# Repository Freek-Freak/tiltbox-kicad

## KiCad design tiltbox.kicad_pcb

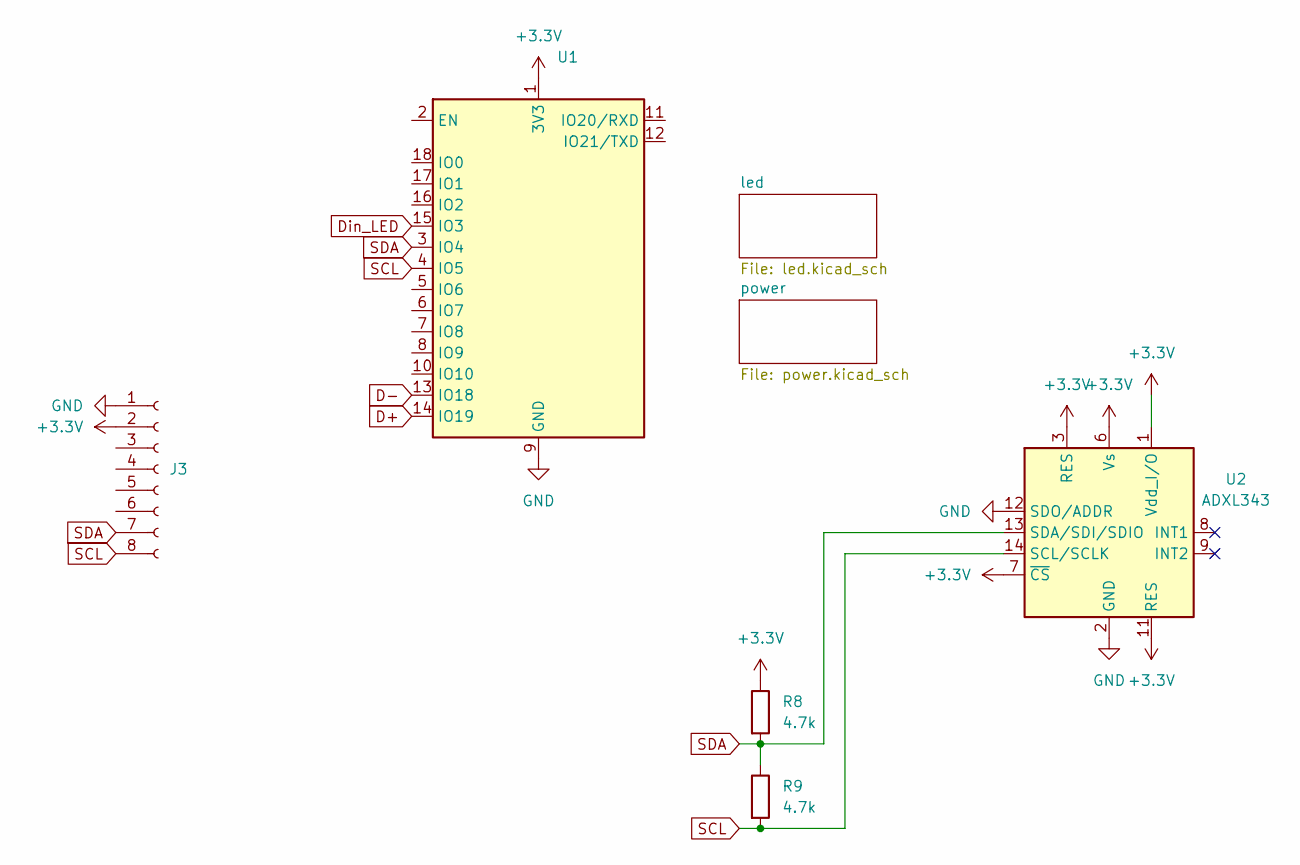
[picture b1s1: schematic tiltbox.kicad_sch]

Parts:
J3: Conn_01x08_Socket; PinHeader_1x08_P2.54mm_Vertical
R8, R9: 4.7k
U1: ESP32-C3-WROOM-02
U2: ADXL343; LGA-14_3x5mm_P0.8mm_LayoutBorder1x6y

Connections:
+3.3V: J3.2, R8.1, U1.1 (3V3), U2.1 (Vdd_I/O), U2.3 (RES), U2.6 (Vs), U2.7 (~CS), U2.11 (RES); also elsewhere on the board
D+: U1.14 (IO19); also elsewhere on the board
D-: U1.13 (IO18); also elsewhere on the board
Din_LED: U1.15 (IO3); also elsewhere on the board
GND: J3.1, U1.9 (GND), U1.19 (GND), U2.2 (GND), U2.4 (GND), U2.5 (GND), U2.12 (SDO/ADDR); also elsewhere on the board
SCL: J3.8, R9.2, U1.4 (IO5), U2.14 (SCL/SCLK)
SDA: J3.7, R8.2, R9.1, U1.3 (IO4), U2.13 (SDA/SDI/SDIO)

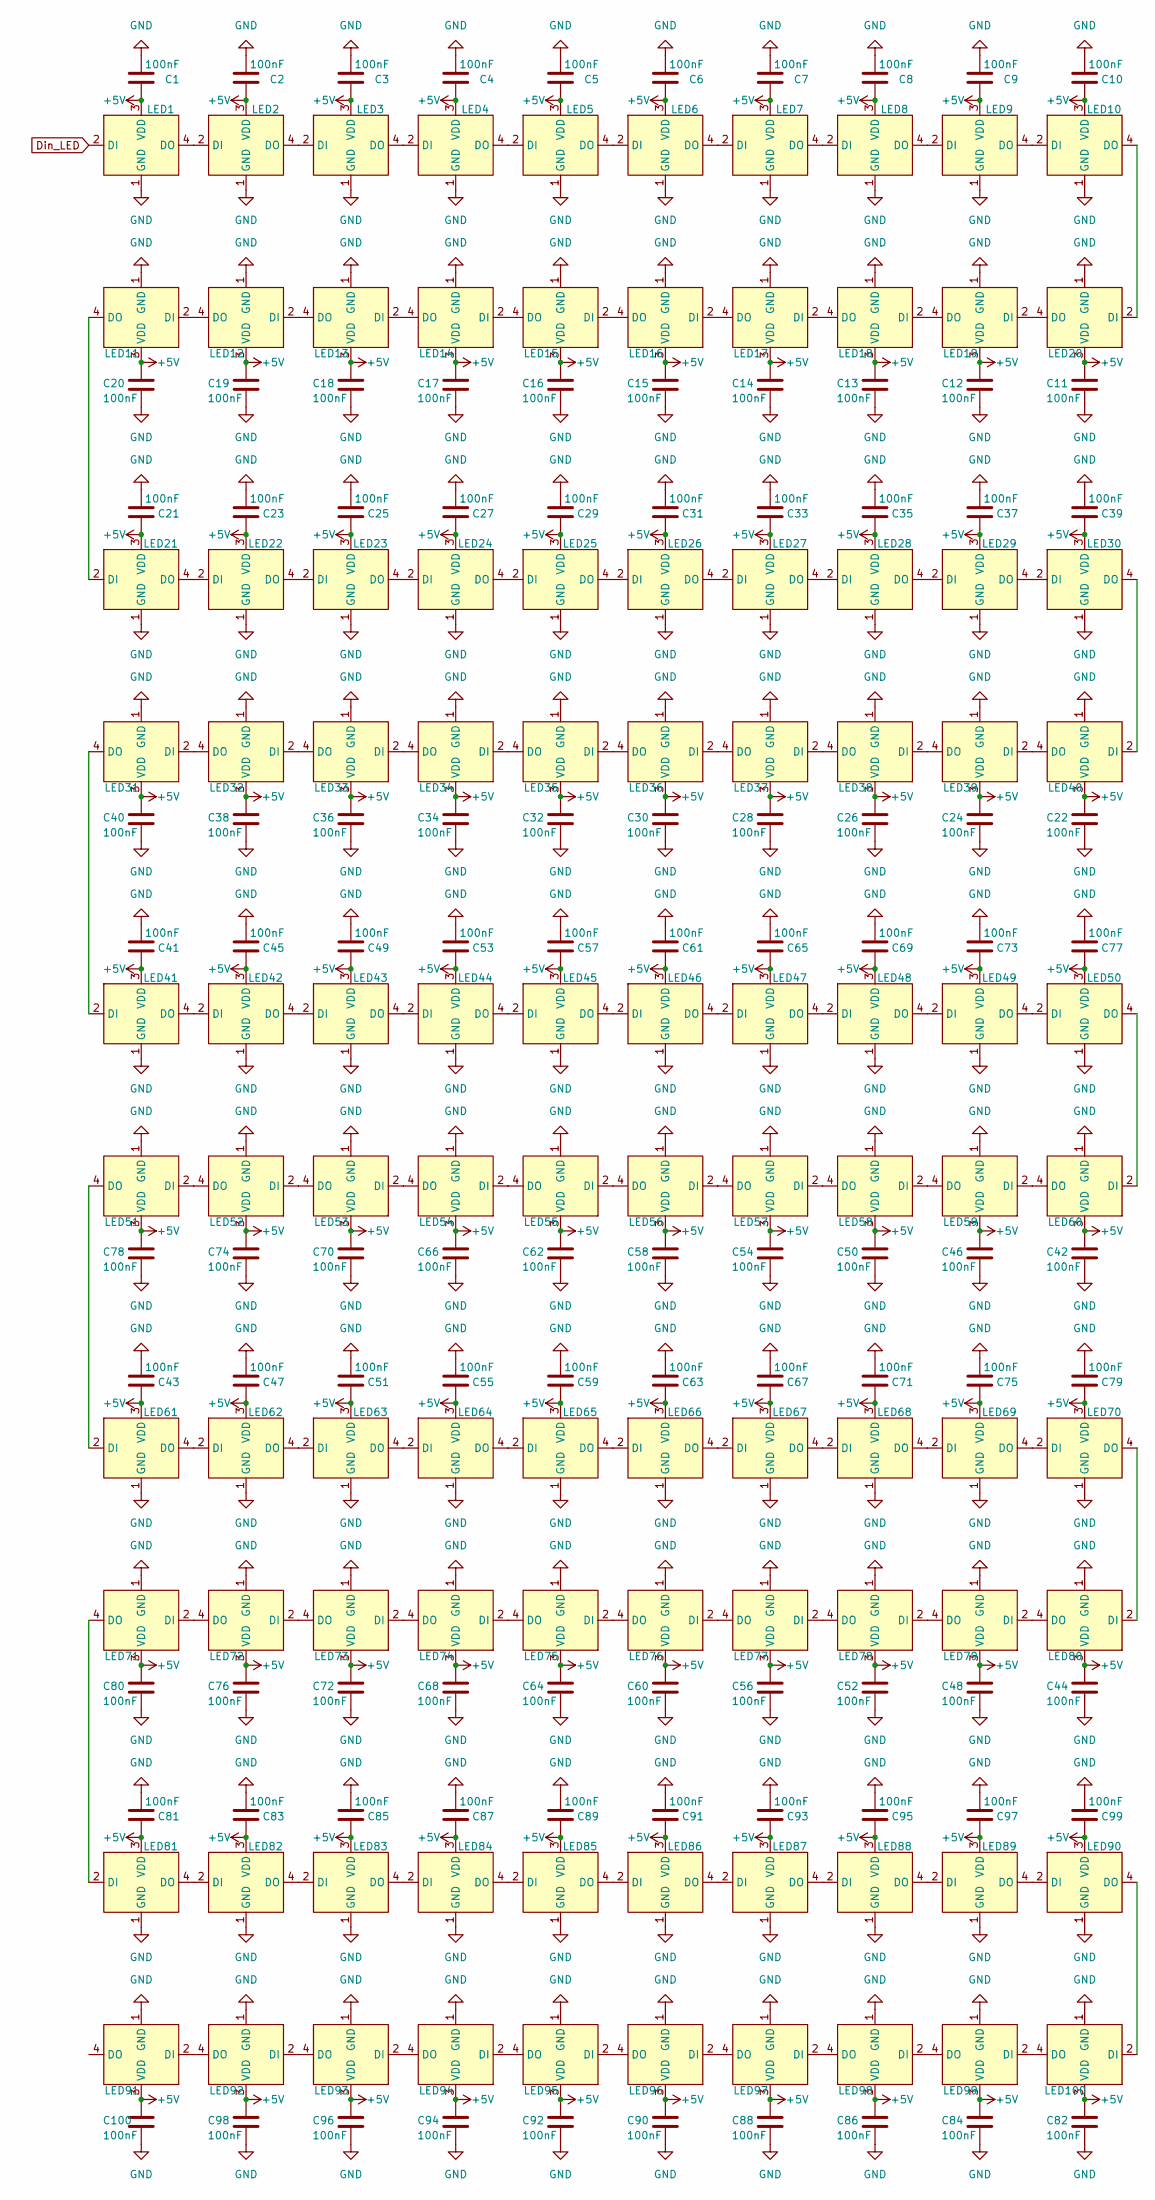
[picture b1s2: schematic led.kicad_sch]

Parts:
C1, C2, C3, C4, C5, C6, C7, C8, C9, C10, C11, C12, C13, C14, C15, C16, C17, C18, C19, C20, C21, C22, C23, C24, C25, C26, C27, C28, C29, C30, C31, C32, C33, C34, C35, C36, C37, C38, C39, C40, C41, C42, C43, C44, C45, C46, C47, C48, C49, C50, C51, C52, C53, C54, C55, C56, C57, C58, C59, C60, C61, C62, C63, C64, C65, C66, C67, C68, C69, C70, C71, C72, C73, C74, C75, C76, C77, C78, C79, C80, C81, C82, C83, C84, C85, C86, C87, C88, C89, C90, C91, C92, C93, C94, C95, C96, C97, C98, C99, C100: 100nF; C_0603_1608Metric; LCSC C14663
LED1, LED2, LED3, LED4, LED5, LED6, LED7, LED8, LED9, LED10, LED11, LED12, LED13, LED14, LED15, LED16, LED17, LED18, LED19, LED20, LED21, LED22, LED23, LED24, LED25, LED26, LED27, LED28, LED29, LED30, LED31, LED32, LED33, LED34, LED35, LED36, LED37, LED38, LED39, LED40, LED41, LED42, LED43, LED44, LED45, LED46, LED47, LED48, LED49, LED50, LED51, LED52, LED53, LED54, LED55, LED56, LED57, LED58, LED59, LED60, LED61, LED62, LED63, LED64, LED65, LED66, LED67, LED68, LED69, LED70, LED71, LED72, LED73, LED74, LED75, LED76, LED77, LED78, LED79, LED80, LED81, LED82, LED83, LED84, LED85, LED86, LED87, LED88, LED89, LED90, LED91, LED92, LED93, LED94, LED95, LED96, LED97, LED98, LED99, LED100: XL-3528RGBW-WS2812B; LED_WS2812B-Mini_PLCC4_3.5x3.5mm; LCSC C2890364

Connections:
+5V: C1.2, C2.2, C3.2, C4.2, C5.2, C6.2, C7.2, C8.2, C9.2, C10.2, C11.2, C12.2, C13.2, C14.2, C15.2, C16.2, C17.2, C18.2, C19.2, C20.2, C21.2, C22.2, C23.2, C24.2, C25.2, C26.2, C27.2, C28.2, C29.2, C30.2, C31.2, C32.2, C33.2, C34.2, C35.2, C36.2, C37.2, C38.2, C39.2, C40.2, C41.2, C42.2, C43.2, C44.2, C45.2, C46.2, C47.2, C48.2, C49.2, C50.2, C51.2, C52.2, C53.2, C54.2, C55.2, C56.2, C57.2, C58.2, C59.2, C60.2, C61.2, C62.2, C63.2, C64.2, C65.2, C66.2, C67.2, C68.2, C69.2, C70.2, C71.2, C72.2, C73.2, C74.2, C75.2, C76.2, C77.2, C78.2, C79.2, C80.2, C81.2, C82.2, C83.2, C84.2, C85.2, C86.2, C87.2, C88.2, C89.2, C90.2, C91.2, C92.2, C93.2, C94.2, C95.2, C96.2, C97.2, C98.2, C99.2, C100.2, LED1.3 (VDD), LED2.3 (VDD), LED3.3 (VDD), LED4.3 (VDD), LED5.3 (VDD), LED6.3 (VDD), LED7.3 (VDD), LED8.3 (VDD), LED9.3 (VDD), LED10.3 (VDD), LED11.3 (VDD), LED12.3 (VDD), LED13.3 (VDD), LED14.3 (VDD), LED15.3 (VDD), LED16.3 (VDD), LED17.3 (VDD), LED18.3 (VDD), LED19.3 (VDD), LED20.3 (VDD), LED21.3 (VDD), LED22.3 (VDD), LED23.3 (VDD), LED24.3 (VDD), LED25.3 (VDD), LED26.3 (VDD), LED27.3 (VDD), LED28.3 (VDD), LED29.3 (VDD), LED30.3 (VDD), LED31.3 (VDD), LED32.3 (VDD), LED33.3 (VDD), LED34.3 (VDD), LED35.3 (VDD), LED36.3 (VDD), LED37.3 (VDD), LED38.3 (VDD), LED39.3 (VDD), LED40.3 (VDD), LED41.3 (VDD), LED42.3 (VDD), LED43.3 (VDD), LED44.3 (VDD), LED45.3 (VDD), LED46.3 (VDD), LED47.3 (VDD), LED48.3 (VDD), LED49.3 (VDD), LED50.3 (VDD), LED51.3 (VDD), LED52.3 (VDD), LED53.3 (VDD), LED54.3 (VDD), LED55.3 (VDD), LED56.3 (VDD), LED57.3 (VDD), LED58.3 (VDD), LED59.3 (VDD), LED60.3 (VDD), LED61.3 (VDD), LED62.3 (VDD), LED63.3 (VDD), LED64.3 (VDD), LED65.3 (VDD), LED66.3 (VDD), LED67.3 (VDD), LED68.3 (VDD), LED69.3 (VDD), LED70.3 (VDD), LED71.3 (VDD), LED72.3 (VDD), LED73.3 (VDD), LED74.3 (VDD), LED75.3 (VDD), LED76.3 (VDD), LED77.3 (VDD), LED78.3 (VDD), LED79.3 (VDD), LED80.3 (VDD), LED81.3 (VDD), LED82.3 (VDD), LED83.3 (VDD), LED84.3 (VDD), LED85.3 (VDD), LED86.3 (VDD), LED87.3 (VDD), LED88.3 (VDD), LED89.3 (VDD), LED90.3 (VDD), LED91.3 (VDD), LED92.3 (VDD), LED93.3 (VDD), LED94.3 (VDD), LED95.3 (VDD), LED96.3 (VDD), LED97.3 (VDD), LED98.3 (VDD), LED99.3 (VDD), LED100.3 (VDD); also elsewhere on the board
Din_LED: LED1.2 (DI); also elsewhere on the board
GND: C1.1, C2.1, C3.1, C4.1, C5.1, C6.1, C7.1, C8.1, C9.1, C10.1, C11.1, C12.1, C13.1, C14.1, C15.1, C16.1, C17.1, C18.1, C19.1, C20.1, C21.1, C22.1, C23.1, C24.1, C25.1, C26.1, C27.1, C28.1, C29.1, C30.1, C31.1, C32.1, C33.1, C34.1, C35.1, C36.1, C37.1, C38.1, C39.1, C40.1, C41.1, C42.1, C43.1, C44.1, C45.1, C46.1, C47.1, C48.1, C49.1, C50.1, C51.1, C52.1, C53.1, C54.1, C55.1, C56.1, C57.1, C58.1, C59.1, C60.1, C61.1, C62.1, C63.1, C64.1, C65.1, C66.1, C67.1, C68.1, C69.1, C70.1, C71.1, C72.1, C73.1, C74.1, C75.1, C76.1, C77.1, C78.1, C79.1, C80.1, C81.1, C82.1, C83.1, C84.1, C85.1, C86.1, C87.1, C88.1, C89.1, C90.1, C91.1, C92.1, C93.1, C94.1, C95.1, C96.1, C97.1, C98.1, C99.1, C100.1, LED1.1 (GND), LED2.1 (GND), LED3.1 (GND), LED4.1 (GND), LED5.1 (GND), LED6.1 (GND), LED7.1 (GND), LED8.1 (GND), LED9.1 (GND), LED10.1 (GND), LED11.1 (GND), LED12.1 (GND), LED13.1 (GND), LED14.1 (GND), LED15.1 (GND), LED16.1 (GND), LED17.1 (GND), LED18.1 (GND), LED19.1 (GND), LED20.1 (GND), LED21.1 (GND), LED22.1 (GND), LED23.1 (GND), LED24.1 (GND), LED25.1 (GND), LED26.1 (GND), LED27.1 (GND), LED28.1 (GND), LED29.1 (GND), LED30.1 (GND), LED31.1 (GND), LED32.1 (GND), LED33.1 (GND), LED34.1 (GND), LED35.1 (GND), LED36.1 (GND), LED37.1 (GND), LED38.1 (GND), LED39.1 (GND), LED40.1 (GND), LED41.1 (GND), LED42.1 (GND), LED43.1 (GND), LED44.1 (GND), LED45.1 (GND), LED46.1 (GND), LED47.1 (GND), LED48.1 (GND), LED49.1 (GND), LED50.1 (GND), LED51.1 (GND), LED52.1 (GND), LED53.1 (GND), LED54.1 (GND), LED55.1 (GND), LED56.1 (GND), LED57.1 (GND), LED58.1 (GND), LED59.1 (GND), LED60.1 (GND), LED61.1 (GND), LED62.1 (GND), LED63.1 (GND), LED64.1 (GND), LED65.1 (GND), LED66.1 (GND), LED67.1 (GND), LED68.1 (GND), LED69.1 (GND), LED70.1 (GND), LED71.1 (GND), LED72.1 (GND), LED73.1 (GND), LED74.1 (GND), LED75.1 (GND), LED76.1 (GND), LED77.1 (GND), LED78.1 (GND), LED79.1 (GND), LED80.1 (GND), LED81.1 (GND), LED82.1 (GND), LED83.1 (GND), LED84.1 (GND), LED85.1 (GND), LED86.1 (GND), LED87.1 (GND), LED88.1 (GND), LED89.1 (GND), LED90.1 (GND), LED91.1 (GND), LED92.1 (GND), LED93.1 (GND), LED94.1 (GND), LED95.1 (GND), LED96.1 (GND), LED97.1 (GND), LED98.1 (GND), LED99.1 (GND), LED100.1 (GND); also elsewhere on the board
unnamed: LED1.4 (DO), LED2.2 (DI)
unnamed: LED2.4 (DO), LED3.2 (DI)
unnamed: LED3.4 (DO), LED4.2 (DI)
unnamed: LED4.4 (DO), LED5.2 (DI)
unnamed: LED5.4 (DO), LED6.2 (DI)
unnamed: LED6.4 (DO), LED7.2 (DI)
unnamed: LED7.4 (DO), LED8.2 (DI)
unnamed: LED8.4 (DO), LED9.2 (DI)
unnamed: LED9.4 (DO), LED10.2 (DI)
unnamed: LED10.4 (DO), LED20.2 (DI)
unnamed: LED11.2 (DI), LED12.4 (DO)
unnamed: LED11.4 (DO), LED21.2 (DI)
unnamed: LED12.2 (DI), LED13.4 (DO)
unnamed: LED13.2 (DI), LED14.4 (DO)
unnamed: LED14.2 (DI), LED15.4 (DO)
unnamed: LED15.2 (DI), LED16.4 (DO)
unnamed: LED16.2 (DI), LED17.4 (DO)
unnamed: LED17.2 (DI), LED18.4 (DO)
unnamed: LED18.2 (DI), LED19.4 (DO)
unnamed: LED19.2 (DI), LED20.4 (DO)
unnamed: LED21.4 (DO), LED22.2 (DI)
unnamed: LED22.4 (DO), LED23.2 (DI)
unnamed: LED23.4 (DO), LED24.2 (DI)
unnamed: LED24.4 (DO), LED25.2 (DI)
unnamed: LED25.4 (DO), LED26.2 (DI)
unnamed: LED26.4 (DO), LED27.2 (DI)
unnamed: LED27.4 (DO), LED28.2 (DI)
unnamed: LED28.4 (DO), LED29.2 (DI)
unnamed: LED29.4 (DO), LED30.2 (DI)
unnamed: LED30.4 (DO), LED40.2 (DI)
unnamed: LED31.2 (DI), LED32.4 (DO)
unnamed: LED31.4 (DO), LED41.2 (DI)
unnamed: LED32.2 (DI), LED33.4 (DO)
unnamed: LED33.2 (DI), LED34.4 (DO)
unnamed: LED34.2 (DI), LED35.4 (DO)
unnamed: LED35.2 (DI), LED36.4 (DO)
unnamed: LED36.2 (DI), LED37.4 (DO)
unnamed: LED37.2 (DI), LED38.4 (DO)
unnamed: LED38.2 (DI), LED39.4 (DO)
unnamed: LED39.2 (DI), LED40.4 (DO)
unnamed: LED41.4 (DO), LED42.2 (DI)
unnamed: LED42.4 (DO), LED43.2 (DI)
unnamed: LED43.4 (DO), LED44.2 (DI)
unnamed: LED44.4 (DO), LED45.2 (DI)
unnamed: LED45.4 (DO), LED46.2 (DI)
unnamed: LED46.4 (DO), LED47.2 (DI)
unnamed: LED47.4 (DO), LED48.2 (DI)
unnamed: LED48.4 (DO), LED49.2 (DI)
unnamed: LED49.4 (DO), LED50.2 (DI)
unnamed: LED50.4 (DO), LED60.2 (DI)
unnamed: LED51.2 (DI), LED52.4 (DO)
unnamed: LED51.4 (DO), LED61.2 (DI)
unnamed: LED52.2 (DI), LED53.4 (DO)
unnamed: LED53.2 (DI), LED54.4 (DO)
unnamed: LED54.2 (DI), LED55.4 (DO)
unnamed: LED55.2 (DI), LED56.4 (DO)
unnamed: LED56.2 (DI), LED57.4 (DO)
unnamed: LED57.2 (DI), LED58.4 (DO)
unnamed: LED58.2 (DI), LED59.4 (DO)
unnamed: LED59.2 (DI), LED60.4 (DO)
unnamed: LED61.4 (DO), LED62.2 (DI)
unnamed: LED62.4 (DO), LED63.2 (DI)
unnamed: LED63.4 (DO), LED64.2 (DI)
unnamed: LED64.4 (DO), LED65.2 (DI)
unnamed: LED65.4 (DO), LED66.2 (DI)
unnamed: LED66.4 (DO), LED67.2 (DI)
unnamed: LED67.4 (DO), LED68.2 (DI)
unnamed: LED68.4 (DO), LED69.2 (DI)
unnamed: LED69.4 (DO), LED70.2 (DI)
unnamed: LED70.4 (DO), LED80.2 (DI)
unnamed: LED71.2 (DI), LED72.4 (DO)
unnamed: LED71.4 (DO), LED81.2 (DI)
unnamed: LED72.2 (DI), LED73.4 (DO)
unnamed: LED73.2 (DI), LED74.4 (DO)
unnamed: LED74.2 (DI), LED75.4 (DO)
unnamed: LED75.2 (DI), LED76.4 (DO)
unnamed: LED76.2 (DI), LED77.4 (DO)
unnamed: LED77.2 (DI), LED78.4 (DO)
unnamed: LED78.2 (DI), LED79.4 (DO)
unnamed: LED79.2 (DI), LED80.4 (DO)
unnamed: LED81.4 (DO), LED82.2 (DI)
unnamed: LED82.4 (DO), LED83.2 (DI)
unnamed: LED83.4 (DO), LED84.2 (DI)
unnamed: LED84.4 (DO), LED85.2 (DI)
unnamed: LED85.4 (DO), LED86.2 (DI)
unnamed: LED86.4 (DO), LED87.2 (DI)
unnamed: LED87.4 (DO), LED88.2 (DI)
unnamed: LED88.4 (DO), LED89.2 (DI)
unnamed: LED89.4 (DO), LED90.2 (DI)
unnamed: LED91.2 (DI), LED92.4 (DO)
unnamed: LED92.2 (DI), LED93.4 (DO)
unnamed: LED93.2 (DI), LED94.4 (DO)
unnamed: LED94.2 (DI), LED95.4 (DO)
unnamed: LED95.2 (DI), LED96.4 (DO)
unnamed: LED96.2 (DI), LED97.4 (DO)
unnamed: LED97.2 (DI), LED98.4 (DO)
unnamed: LED98.2 (DI), LED99.4 (DO)
unnamed: LED90.4 (DO), LED100.2 (DI)
unnamed: LED99.2 (DI), LED100.4 (DO)

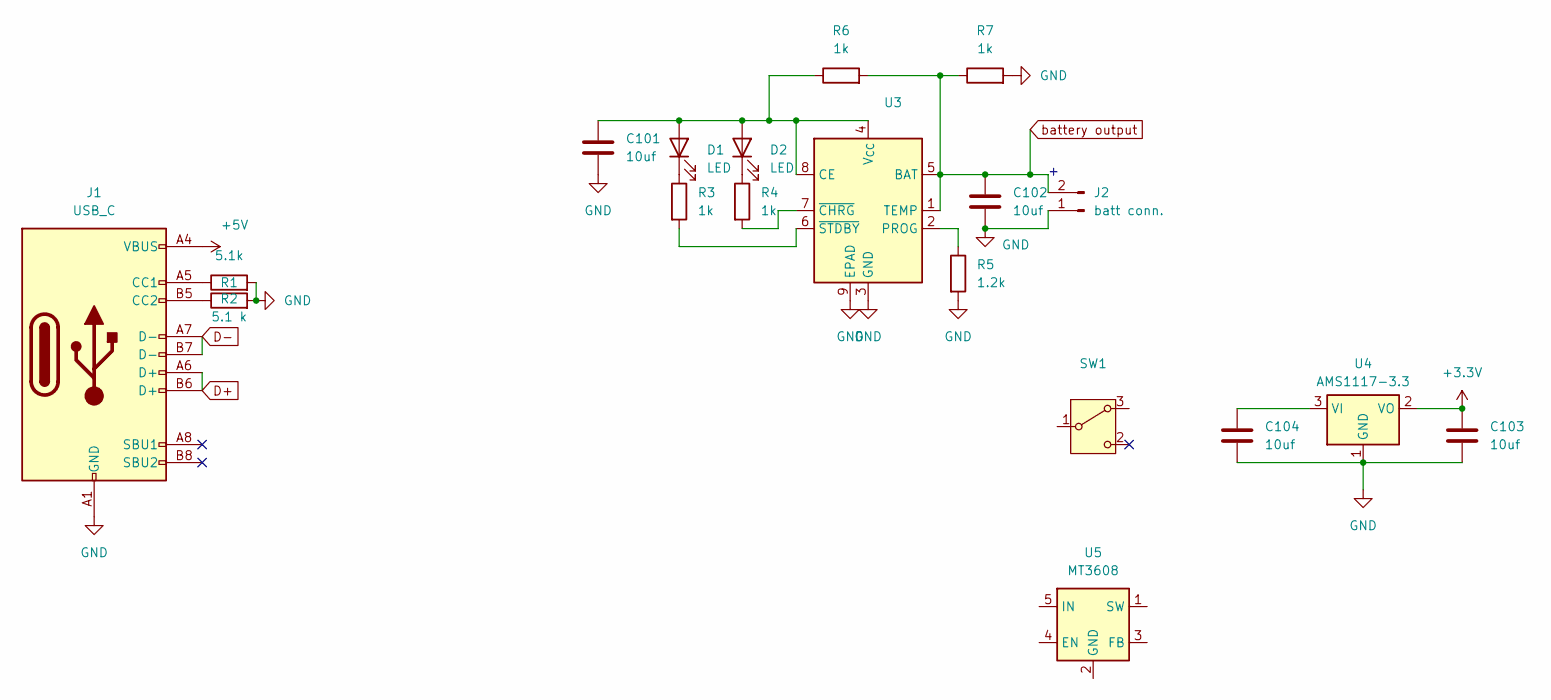
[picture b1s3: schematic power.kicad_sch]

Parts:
C101, C102, C103, C104: 10uf; C_0805_2012Metric
D1, D2: LED; LED_0805_2012Metric
J1: USB_C; USB_C_Receptacle_GCT_USB4110
J2: batt conn.; JST_PH_S2B-PH-K_1x02_P2.00mm_Horizontal
R1: 5.1k; R_0805_2012Metric
R2: 5.1 k; R_0805_2012Metric
R3, R4, R6, R7: 1k; R_0805_2012Metric
R5: 1.2k; R_0805_2012Metric
SW1: SW_Wuerth_450301014042; SW_Slide-03_Wuerth-WS-SLTV_10x2.5x6.4_P2.54mm
U3: TP4056-42-ESOP8; SOIC-8-1EP_3.9x4.9mm_P1.27mm_EP2.41x3.3mm_ThermalVias
U4: AMS1117-3.3; SOT-223-3_TabPin2
U5: MT3608; SOT-23-6

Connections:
5v output: C104.1, SW1.3 (A), U4.3 (VI)
+3.3V: C103.1, U4.2 (VO); also elsewhere on the board
+5V: J1.A4 (VBUS), J1.A9 (VBUS), J1.B4 (VBUS), J1.B9 (VBUS); also elsewhere on the board
D+: J1.A6 (D+), J1.B6 (D+); also elsewhere on the board
D-: J1.A7 (D-), J1.B7 (D-); also elsewhere on the board
GND: C101.2, C102.2, C103.2, C104.2, J1.A1 (GND), J1.A12 (GND), J1.B1 (GND), J1.B12 (GND), J2.1, R1.2, R2.2, R5.2, R7.2, U3.3 (GND), U3.9 (EPAD), U4.1 (GND); also elsewhere on the board
unnamed: C101.1, D1.2 (A), D2.2 (A), R6.1, U3.4 (V_{CC}), U3.8 (CE)
unnamed: D1.1 (K), R3.1
unnamed: D2.1 (K), R4.1
unnamed: J1.A5 (CC1), R1.1
unnamed: J1.B5 (CC2), R2.1
unnamed: R5.1, U3.2 (PROG)
unnamed: R4.2, U3.7 (~CHRG)
unnamed: R3.2, U3.6 (~STDBY)
battery output 5v: C102.1, J2.2, R6.2, R7.1, SW1.1 (B), U3.1 (TEMP), U3.5 (BAT)

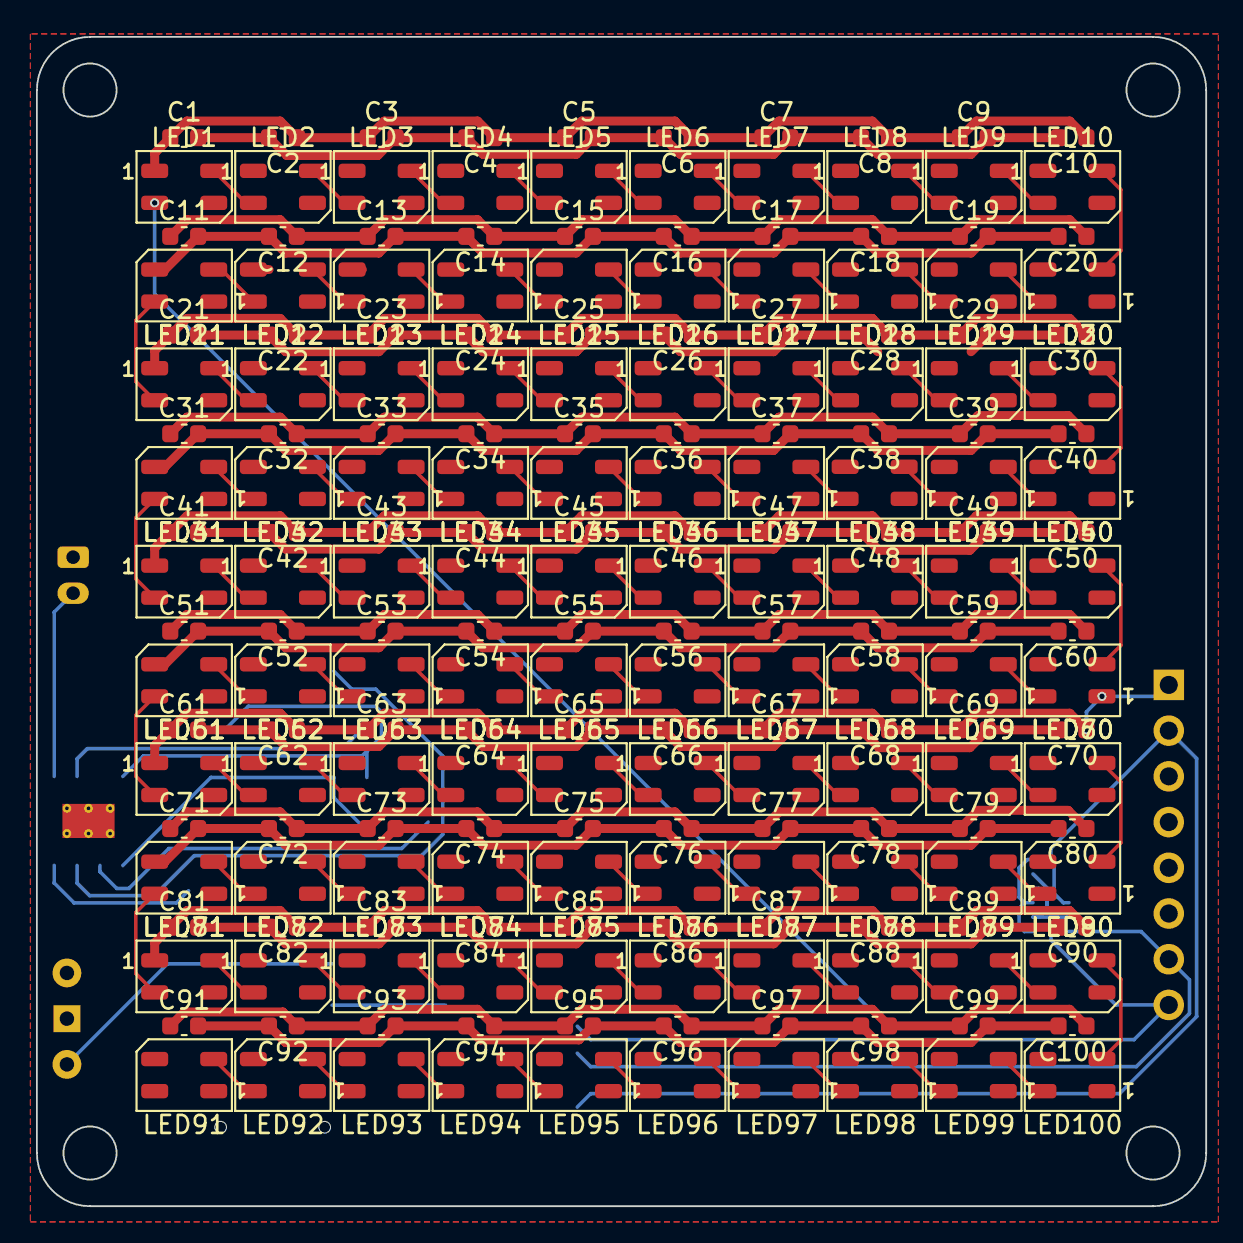
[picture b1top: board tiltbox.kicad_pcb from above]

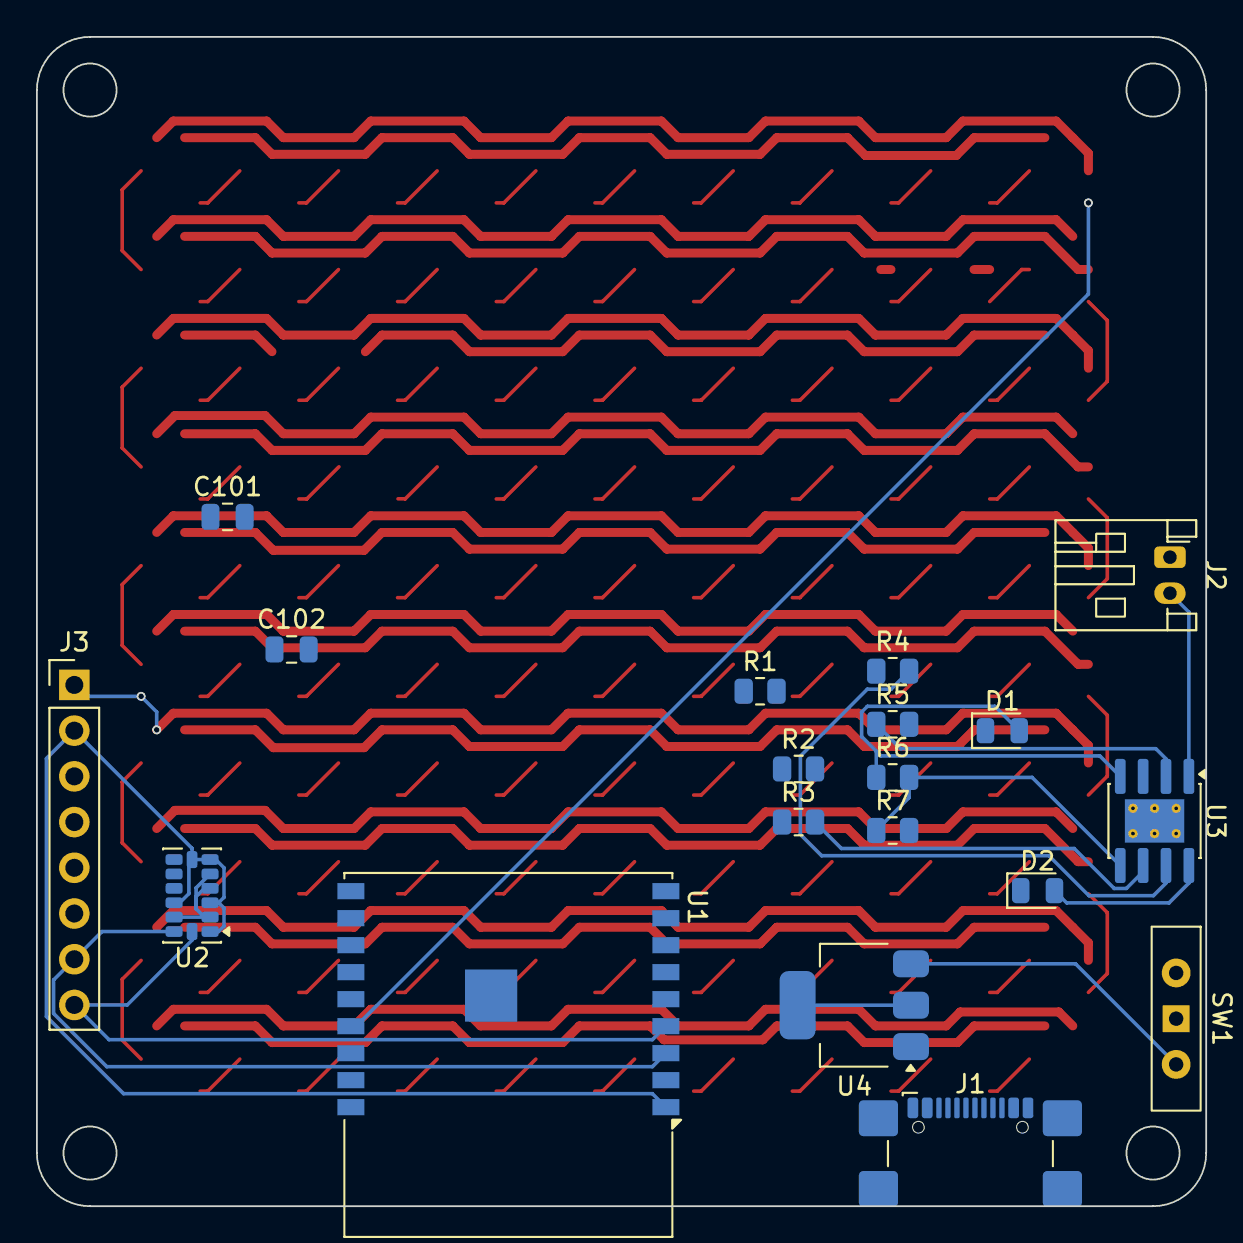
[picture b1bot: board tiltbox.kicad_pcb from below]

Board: 4 copper layers, 65.0 x 65.0 mm, 219 parts (19 on the bottom side), 117 nets.

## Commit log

2026-04-15 files erbij
2026-04-15 moved esp
2026-04-15 verqndering
2026-04-15 verder gewerkt aan pcb
2026-04-16 ceep out zone
